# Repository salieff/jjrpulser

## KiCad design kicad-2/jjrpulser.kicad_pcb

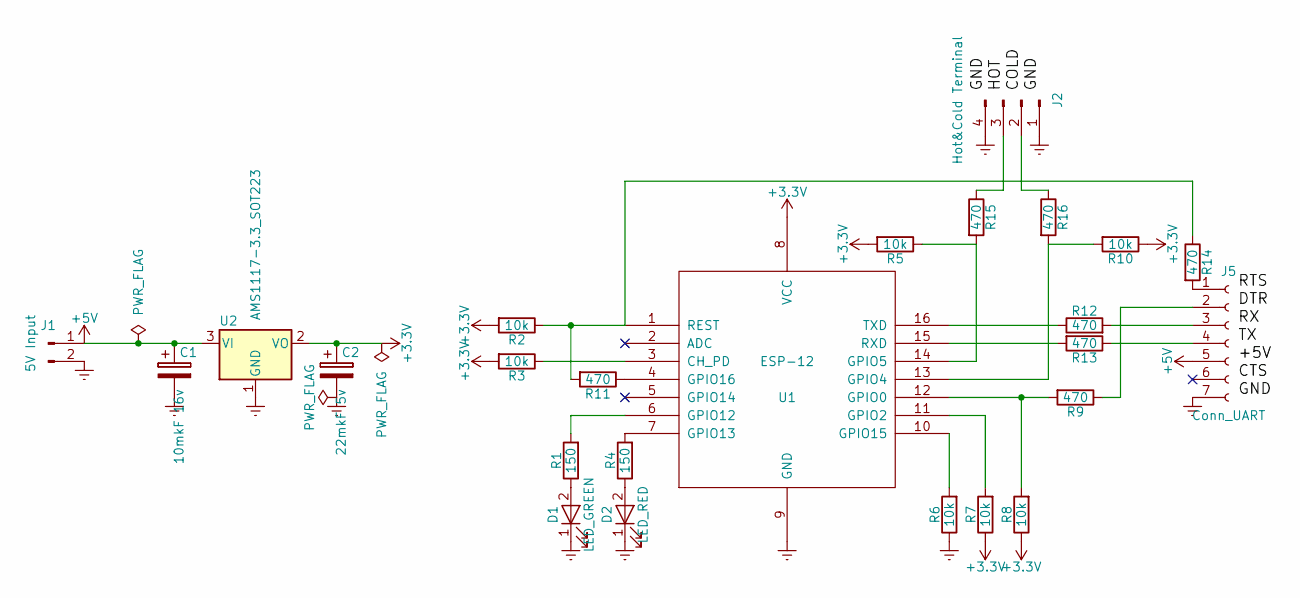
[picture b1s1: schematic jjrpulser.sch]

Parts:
C1: 10mkF 16v; CP_Tantalum_Case-A_EIA-3216-18_Reflow
C2: 22mkF 5v; CP_Tantalum_Case-A_EIA-3216-18_Reflow
D1: LED_GREEN; LED_D3.0mm
D2: LED_RED; LED_D3.0mm
J1: 5V Input; JST_PH_S2B-PH-K_02x2.00mm_Angled
J2: Hot&Cold Terminal; JST_PH_S4B-PH-K_04x2.00mm_Angled
J5: Conn_UART; Socket_Strip_Angled_1x07_Pitch2.54mm
R1, R4: 150; R_0805_HandSoldering
R2, R3, R6, R7, R8: 10k; R_0805_HandSoldering
R5, R10: 10k; R_1206_HandSoldering
R9, R11, R12, R13, R14, R15, R16: 470; R_0805_HandSoldering
U1: ESP-12
U2: AMS1117-3.3_SOT223; SOT-223-3Lead_TabPin2

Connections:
+3V3: C2.1, R2.2, R3.2, R5.2, R7.1, R8.1, R10.1, U1.8 (VCC), U2.2 (VO)
+5V: C1.1, J1.1, J5.5, U2.3 (VI)
Earth: C1.2, C2.2, D1.1 (K), D2.1 (K), J1.2, J2.1, J2.4, J5.7, R6.1, U1.9 (GND), U2.1 (GND)
unnamed: D1.2 (A), R1.1
unnamed: D2.2 (A), R4.1
unnamed: J2.2, R16.1
unnamed: J2.3, R15.1
unnamed: J5.1, R14.2
unnamed: J5.2, R9.1
unnamed: J5.3, R12.2
unnamed: J5.4, R13.1
unnamed: R1.2, U1.6 (GPIO12)
unnamed: R3.1, U1.3 (CH_PD)
unnamed: R4.2, U1.7 (GPIO13)
unnamed: R6.2, U1.10 (GPIO15)
unnamed: R7.2, U1.11 (GPIO2)
unnamed: R8.2, R9.2, U1.12 (GPIO0)
unnamed: R10.2, R16.2, U1.13 (GPIO4)
unnamed: R11.1, U1.4 (GPIO16)
unnamed: R2.1, R11.2, R14.1, U1.1 (REST)
unnamed: R12.1, U1.16 (TXD)
unnamed: R13.2, U1.15 (RXD)
unnamed: R5.1, R15.2, U1.14 (GPIO5)

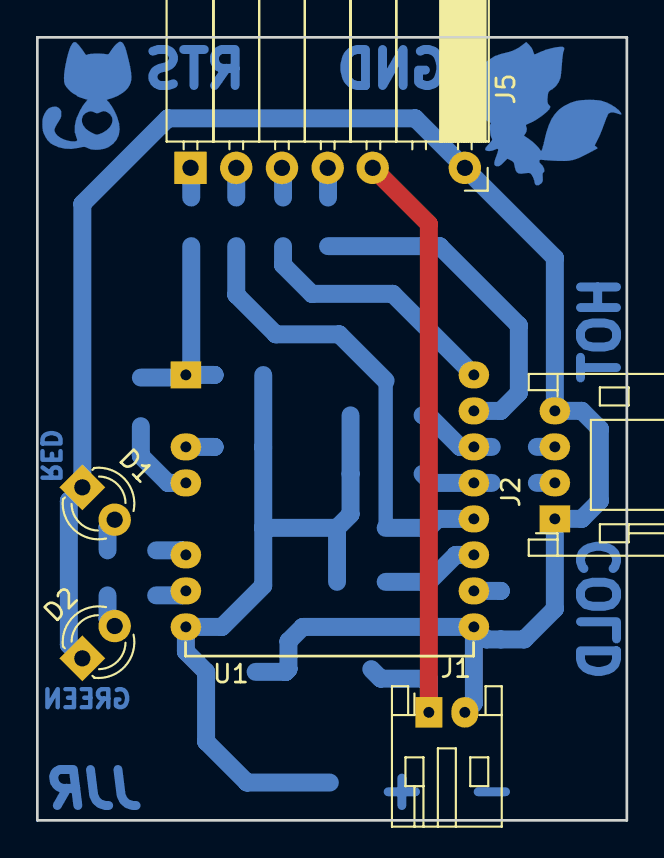
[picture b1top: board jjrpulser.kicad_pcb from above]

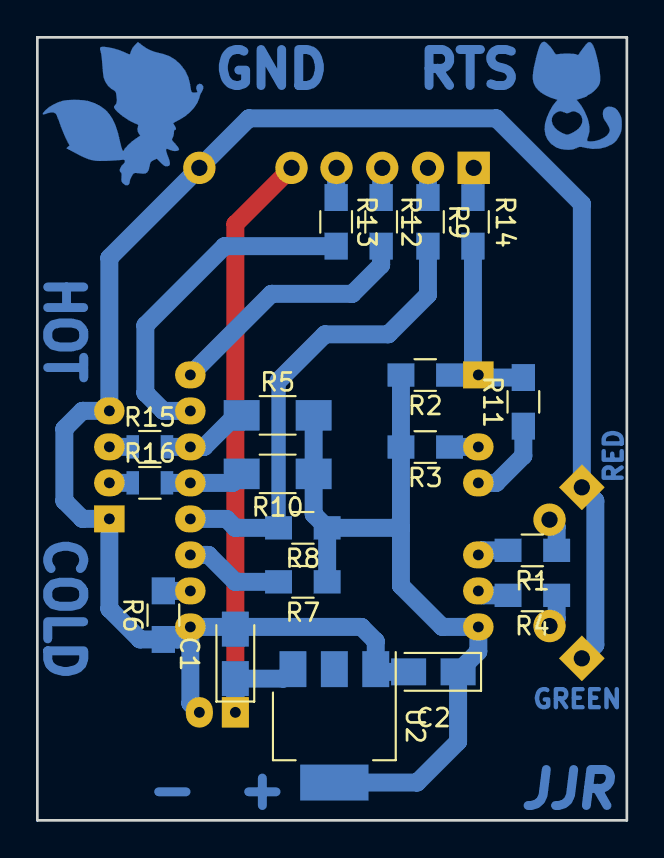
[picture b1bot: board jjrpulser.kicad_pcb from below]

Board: 2 copper layers, 32.8 x 43.5 mm, 27 parts (19 on the bottom side), 23 nets.

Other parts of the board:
Ref**: Val**; 1296354
Ref**#2: Val**; cute_kittens_vector_set

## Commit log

2018-10-26 Скорость консоли в 74880, чтобы было видно boot message. Режимы лампочек переключаются из консоли, зеленая - 01234 и красная - gasdf
2018-10-26 Простые примеры на нажатия кнопок (с дребезгом) и зажигание светодиодов.
2018-11-07 Начало реализации соединения с сервером
2018-11-08 Реализация соединения с Wi-Fi
2018-11-09 Асинхронная посылка импульсов на HTTP-сервер. Добавлены библиотеки ESPAsyncTCP и asyncHTTPrequest. Дефолтная стабилизация PinBouncer уменьшена до 500мс. Эмуляция hot и cold импульсов из консоли, клав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
2018-11-12 Вывод uptime по клавише u. Вывод free heap по клавише m. Нагрузочное тестирование - 3 запроса каждые 15 сек. Список параллельных HTTP-запросов. Рефакторинг, фиксы.
2018-11-13 Добавлено количество ошибок HTTP в статистику uptime. Реализация списка соединений, как статического массива (вместо вектора). Избавляемся от паттерна SingleTone в DataStorage. Избавляемся от STL. Не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
2018-11-14 New/delete mismatch fixed
2018-11-16 Своя реализация HTTP GET, максимально простая и безглючная
2018-11-18 State-machine для TCP-соединения
2018-11-19 Доработка и отладка HTTPRequest. WIP
2018-11-20 Реализация парсинга HTTP
2018-11-20 Асинхронные HTTP/GET запросы дописаны до рабочего состояния. ESPAsyncTCP и asyncHTTPrequest удалены и заменены своей реализацией
2018-11-21 Маленькая адаптация под LWIP2
2018-11-22 Реализован setup со стороны сервера. Исправления.
2018-11-23 Эксперименты и мелкие улучшения
2018-11-28 Серверная часть
2018-11-28 Поддержка отображения, хранения и передачи настроек в устройство
2018-11-28 Немного порядка
2018-12-07 Тотальный переход на MySQL. Рефакторинг.
2018-12-08 Новый тип графиков
2018-12-08 Наводим красоту
2018-12-09 Рефакторинг
2018-12-14 Защита от фальшивого setup при сбое базы. Наведение красоты.
2018-12-14 Сохранение показаний в EEPROM. Выключены лишние дебаги.
2018-12-21 Удалена забытая копипаста. Увеличены таймауты.
2018-12-24 Хранение setup для отправки в контроллер перенесено в файл для разгрузки БД. Timestamps и принудительный 0 по Y на графиках.
2018-12-24 Для ReadSetupCounters добавлен softmode, чтобы web-интерфейс не стирал при чтении setup, который сам же и записал.
2019-02-09 Распихали переменные по структурам. Подготовка к переезду статистики в storage.cpp и ее отправки на сервер
2019-03-11 Отсылка статистики на сервер. WIP
2019-03-12 Отсылка статистики на сервер. Рефакторинг
2019-03-25 Перенос сервера на NanoPi Fire3
2019-03-27 Бэкэнд для статистики. WIP.
2019-03-27 Отображение статистики на фронтэнде
2019-03-27 Утилита для нагрузочного тестирования сервера
2019-03-27 Наглядное дублирование статистики в ответе на запрос. Параллельные запросы в стресс-тесте.
2019-03-28 Фикс парсинга аптайма в начале суток. Запросы убраны из фона, потому что тогда счетчики не считаются.
2019-03-31 Улучшен запрос потребления по периодам
2019-04-02 Документация. Пример кронтаба
2019-04-03 Документация WIP
2019-04-13 Документация W.I.P
2019-04-13 Документация. Глава про blinker.cpp
2019-04-17 PDF para leer comodo
2019-04-19 Документация: глава про PinBouncer
2019-05-06 Документация WIP. Схемотехника для Kicad.
2019-05-08 Расстояние между ножками блока питания уменьшено до 47мм
2019-05-08 Мелкие улучшения трассировки
2019-05-09 Еще немного гламура в трассировку
2019-05-20 Документация. Описаны макросы, внутренние переменные и блок EEPROM-функций для модуля DataStorage
2019-05-24 Документация по модулю DataStorage. Описаны функции-обрабочики Wi-FI, функции работы с HTTP-запросами и со статистикой
2019-06-11 Более плотная разводка
2019-06-13 Оптимизированная разводка с интегрированным питанием
2019-06-14 Разводка в процессе
2019-06-17 Новая разводка: замена micro-USB на обычный разъем питания
2019-06-17 Новая разводка - WIP
2019-06-18 Разводка2: +5V с UART - программирование и консоль без внешнего питания. GPIO16 <--> RESET - выход из deep sleep
2019-06-19 Разводка2: Забытые упоминания R2010 заменены на R1206
2019-06-21 Новая разводка
2019-06-21 Разводка2: Защитные резисторы на подключении водосчетчиков
2019-06-22 Демонстрационный скетч с ШИМ на OUTPUT GPIO
2019-06-28 Новые маленькие коннекторы для счетчиков и питания
2019-07-02 Новая разводка. Котик и лисичка.
2019-07-10 Новая разводка: буквы и размеры
2019-12-19 Improved and extended WebServer example
2019-12-19 Extract passwords to external file
2019-12-19 Forget about passwors.h
2019-12-19 Glue frontend and backend together
2019-12-27 COMET WIP
2019-12-29 Забытые файлы
2019-12-30 Рабочая реалиация COMET на long poll-ах
2020-03-13 Files for new ESP32 project
2020-03-13 Forgotten scheme
2020-03-14 Подавление избыточных COMET-событий экономит трафик
2020-03-15 Touch buttons added
